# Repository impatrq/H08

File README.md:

# H-08

Reacondicionamiento aviónico del Sikorsky S-55 de la escuela. Proyecto de 7.º 1.ª, Aviónica, comisión B, de la E.E.S.T. N° 7 "IMPA" (Taller Regional Quilmes), 2026.

- Página: [proyecto-h08.github.io](https://proyecto-h08.github.io/)
- Instagram: [@proyectoh08](https://www.instagram.com/proyectoh08/)
- Mail: h08proyecto2026@gmail.com
- Video de presentación: [YouTube](https://www.youtube.com/watch?v=HCQF5zqOE_o)

## Qué es

H-08 es la matrícula de un Sikorsky S-55 (H-19A) que está en el taller de la escuela. Casi todos los instrumentos originales ya no funcionan, así que armamos el tablero de nuevo para usarlo en clase. Sobre la chapa original van 21 instrumentos con piezas que imprimimos en 3D, y las agujas las mueven servos SG90. La brújula usa un motor paso a paso y hay seis luces de alerta.

Todo lo maneja una Raspberry Pi 5. Tiene un modelo simple del helicóptero (motor, rotor, transmisión, aceite, combustible, parte eléctrica y actitud) y con eso calcula qué tiene que marcar cada instrumento. El profesor elige la fase del vuelo y mete fallas desde el celular, por ejemplo una falla de generador o de bomba de aceite, y los alumnos ven cómo responde cada aguja en el tablero y en su celular.

La Raspberry arma su propia red wifi, así que no hace falta internet:

- red: Tablero-H08
- clave: sikorsky55
- dirección: http://10.55.0.1 (en la mayoría de los celulares se abre sola al conectarse)

## Cómo está armado

La Raspberry habla por I2C con dos placas PCA9685 (direcciones 0x40 y 0x41) que generan el pulso de los 20 servos y prenden las luces. El motor de la brújula es un 28BYJ-48 con su driver ULN2003, conectado a los GPIO 12, 16, 20 y 21. La llave BATERÍA del panel va al GPIO 26 y sirve para apagar todo en orden. Los servos se alimentan aparte, nunca desde la Pi: una fuente de 12 V alimenta un regulador LM2596 que baja a 5 V.

Las conexiones pasan por una placa madre que diseñamos en KiCad (170 x 110 mm, una sola cara).

En los instrumentos donde la aguja tiene que dar más vuelta que lo que gira un servo usamos engranajes impresos: 36/24, 40/24 y 48/24. El horizonte artificial muestra solo el alabeo: el plato va pegado al servo. La brújula gira sin fin con el paso a paso.

La pantalla HDMI de la Raspberry muestra el tablero completo, con las mismas carátulas que pegamos en los instrumentos y un helicóptero en 3D que vuela con la simulación.

## Carpetas

- [Docs](Docs/): carpeta técnica, carpeta de campo, manual de usuario, elementos de alcance inconclusos, anteproyecto e historias de usuario.
- [Kicad](Kicad/): el proyecto de la placa madre y los planos para hacerla.
- [Software](Software/): el programa de la Raspberry Pi 5.
- [Estructura](Estructura/): las piezas para imprimir (STL), las carátulas y cómo se arma cada instrumento.
- [Web](Web/): la página del proyecto.
- [Multimedia](Multimedia/): video de presentación, las diapositivas de la expo, fotos (la del equipo también), logos, banner y stickers.

## Lo que usamos

| Componente | Cant. |
|---|---|
| Raspberry Pi 5 de 4 GB con fuente oficial de 27 W | 1 |
| MicroSD de 16 GB | 1 |
| PCA9685 | 2 |
| Servo SG90 | 20 |
| Motor 28BYJ-48 con driver ULN2003 | 1 |
| LED 5 mm (ámbar, rojo y verde) | 6 |
| Fuente de 12 V 7 A | 1 |
| Regulador LM2596 (de 12 V a 5 V) | 1 |
| Llave de palanca (BATERÍA) | 1 |
| Pantalla HDMI | 1 |
| Placa madre | 1 |

Más las piezas impresas en PLA, los acrílicos de cada instrumento y los pegamentos. La lista completa con precios está en [Docs/Plantilla_de_compras_H08.xlsx](Docs/Plantilla_de_compras_H08.xlsx).

## Para ponerlo en marcha

Primero se imprimen y arman los instrumentos con las piezas de Estructura, y se hace la placa con los planos de Kicad/Planos.

Después se copia `Software/H08_Pi5` a la Raspberry, que tiene que tener Raspberry Pi OS con escritorio de 64 bits, y se instala:

```bash
cd ~/H08_Pi5/raspberry_pi5
bash instalar.sh
sudo reboot
```

Con `python3 diagnostico_pi.py` se revisan las conexiones y con `python3 calibrar_instrumento.py --todos` se calibran las agujas una por una. Todo eso está explicado más largo en [Software/H08_Pi5/LEEME.md](Software/H08_Pi5/LEEME.md) y en el manual de usuario.

## Equipo

- Mateo Ghirelli: software (programa en Python, WiFi y simulación)
- Fausto Taranto: hardware (circuito, calibración y cableado)
- Constantino da Costa: integración, pruebas, redes y presentación
- Thomas Lehmann: restauración mecánica y montaje
- Agustín Merodo: relevamiento, montaje y documentación

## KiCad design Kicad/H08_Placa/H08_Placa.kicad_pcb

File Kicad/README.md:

# Placa madre

El proyecto de KiCad de la placa madre del tablero: esquemático y placa ruteada, con las librerías que hicimos adentro de la misma carpeta.

En `H08_Placa` está el proyecto. Se abre `H08_Placa.kicad_pro` y con eso aparecen el esquemático y la placa. Las librerías propias son `H08.kicad_sym` (símbolos) y la carpeta `H08.pretty` (huellas con las medidas de los componentes reales). `CONEXIONES.txt` tiene la red completa pata por pata y en `LEEME.txt` está el detalle del diseño y los pasos para hacerla.

En `Planos` están los PDF para fabricarla: el arte del cobre espejado para planchar, el cobre visto desde abajo, el plano de agujeros y el de montaje (dónde va cada componente).

La placa mide 170 x 110 mm y es de una sola cara. Tiene 242 pistas y 25 puentes de alambre, que son 15 del ruteo y 10 para coser el plano de masa. A la entrada de 5 V lleva un fusible lento de 4 A (F1) y después un supresor P6KE6.8A (D2).

Para abrirla usamos KiCad 10. El proyecto está guardado en formato de KiCad 6, así que la primera vez pregunta si lo actualiza y se le dice que sí. No hay que instalar ninguna librería. Al abrir la placa hay que apretar B para que rellene el plano de masa.

Para hacerla no hace falta exportar nada: `Planos/arte_bcu_espejado.pdf` ya está a escala 1:1. Antes de transferirlo conviene medir el contorno con una regla, tiene que dar 170 x 110 mm. Se imprime al 100 %, no con "ajustar a la página".

En la placa que armamos no van U1 y U2 (los ULN2003) ni las borneras J11 y J12 de los motores. El motor de la brújula usa la plaquita ULN2003 que viene con él y se conecta con cables a los pines que pusimos en el lugar de U2.

**Ojo con el conector de la Raspberry (J1).** Cuando hicimos la placa, el dibujo quedó dado vuelta, como en un espejo. Por eso los pines de J1 no quedaron en el mismo orden que los de la Raspberry, y el cable plano de 40 hilos no sirve: conectaría cada señal en el lugar equivocado.

Lo resolvimos con cables sueltos (Dupont hembra-hembra), uno por pin. Cada cable une el pin de la Raspberry con el pin de la placa que tiene el mismo nombre, por ejemplo SDA con SDA. El nombre de cada pin está escrito en la placa. La lista de qué va con qué está en [Software/H08_Pi5/LEEME.md](../Software/H08_Pi5/LEEME.md#cableado-de-la-raspberry-a-la-placa-madre).

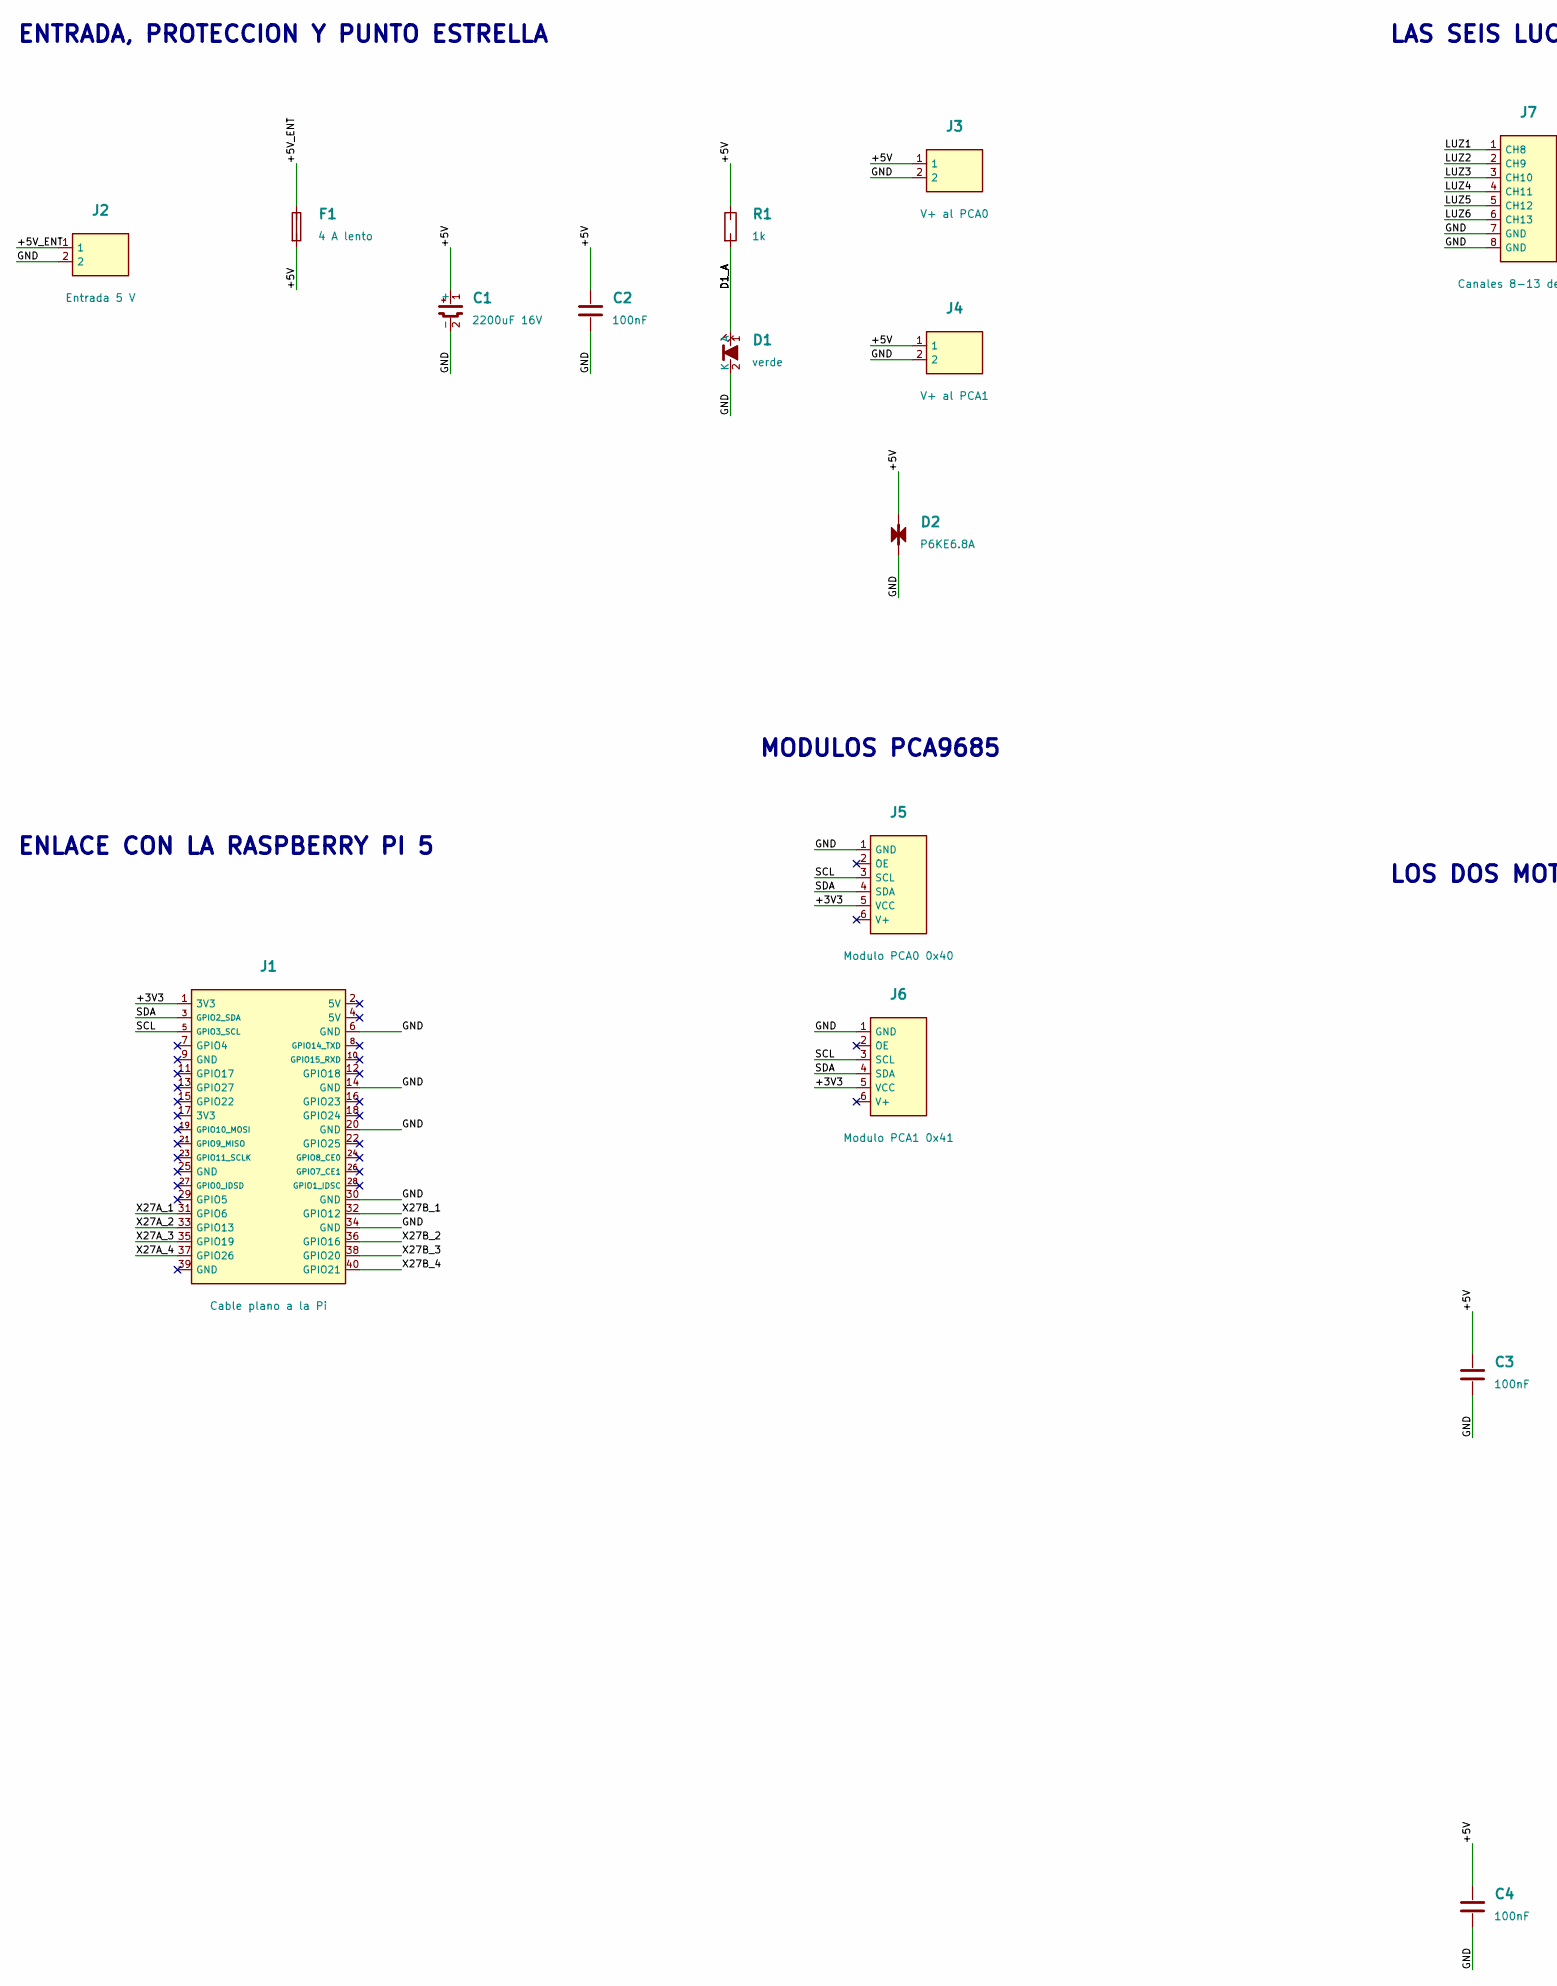
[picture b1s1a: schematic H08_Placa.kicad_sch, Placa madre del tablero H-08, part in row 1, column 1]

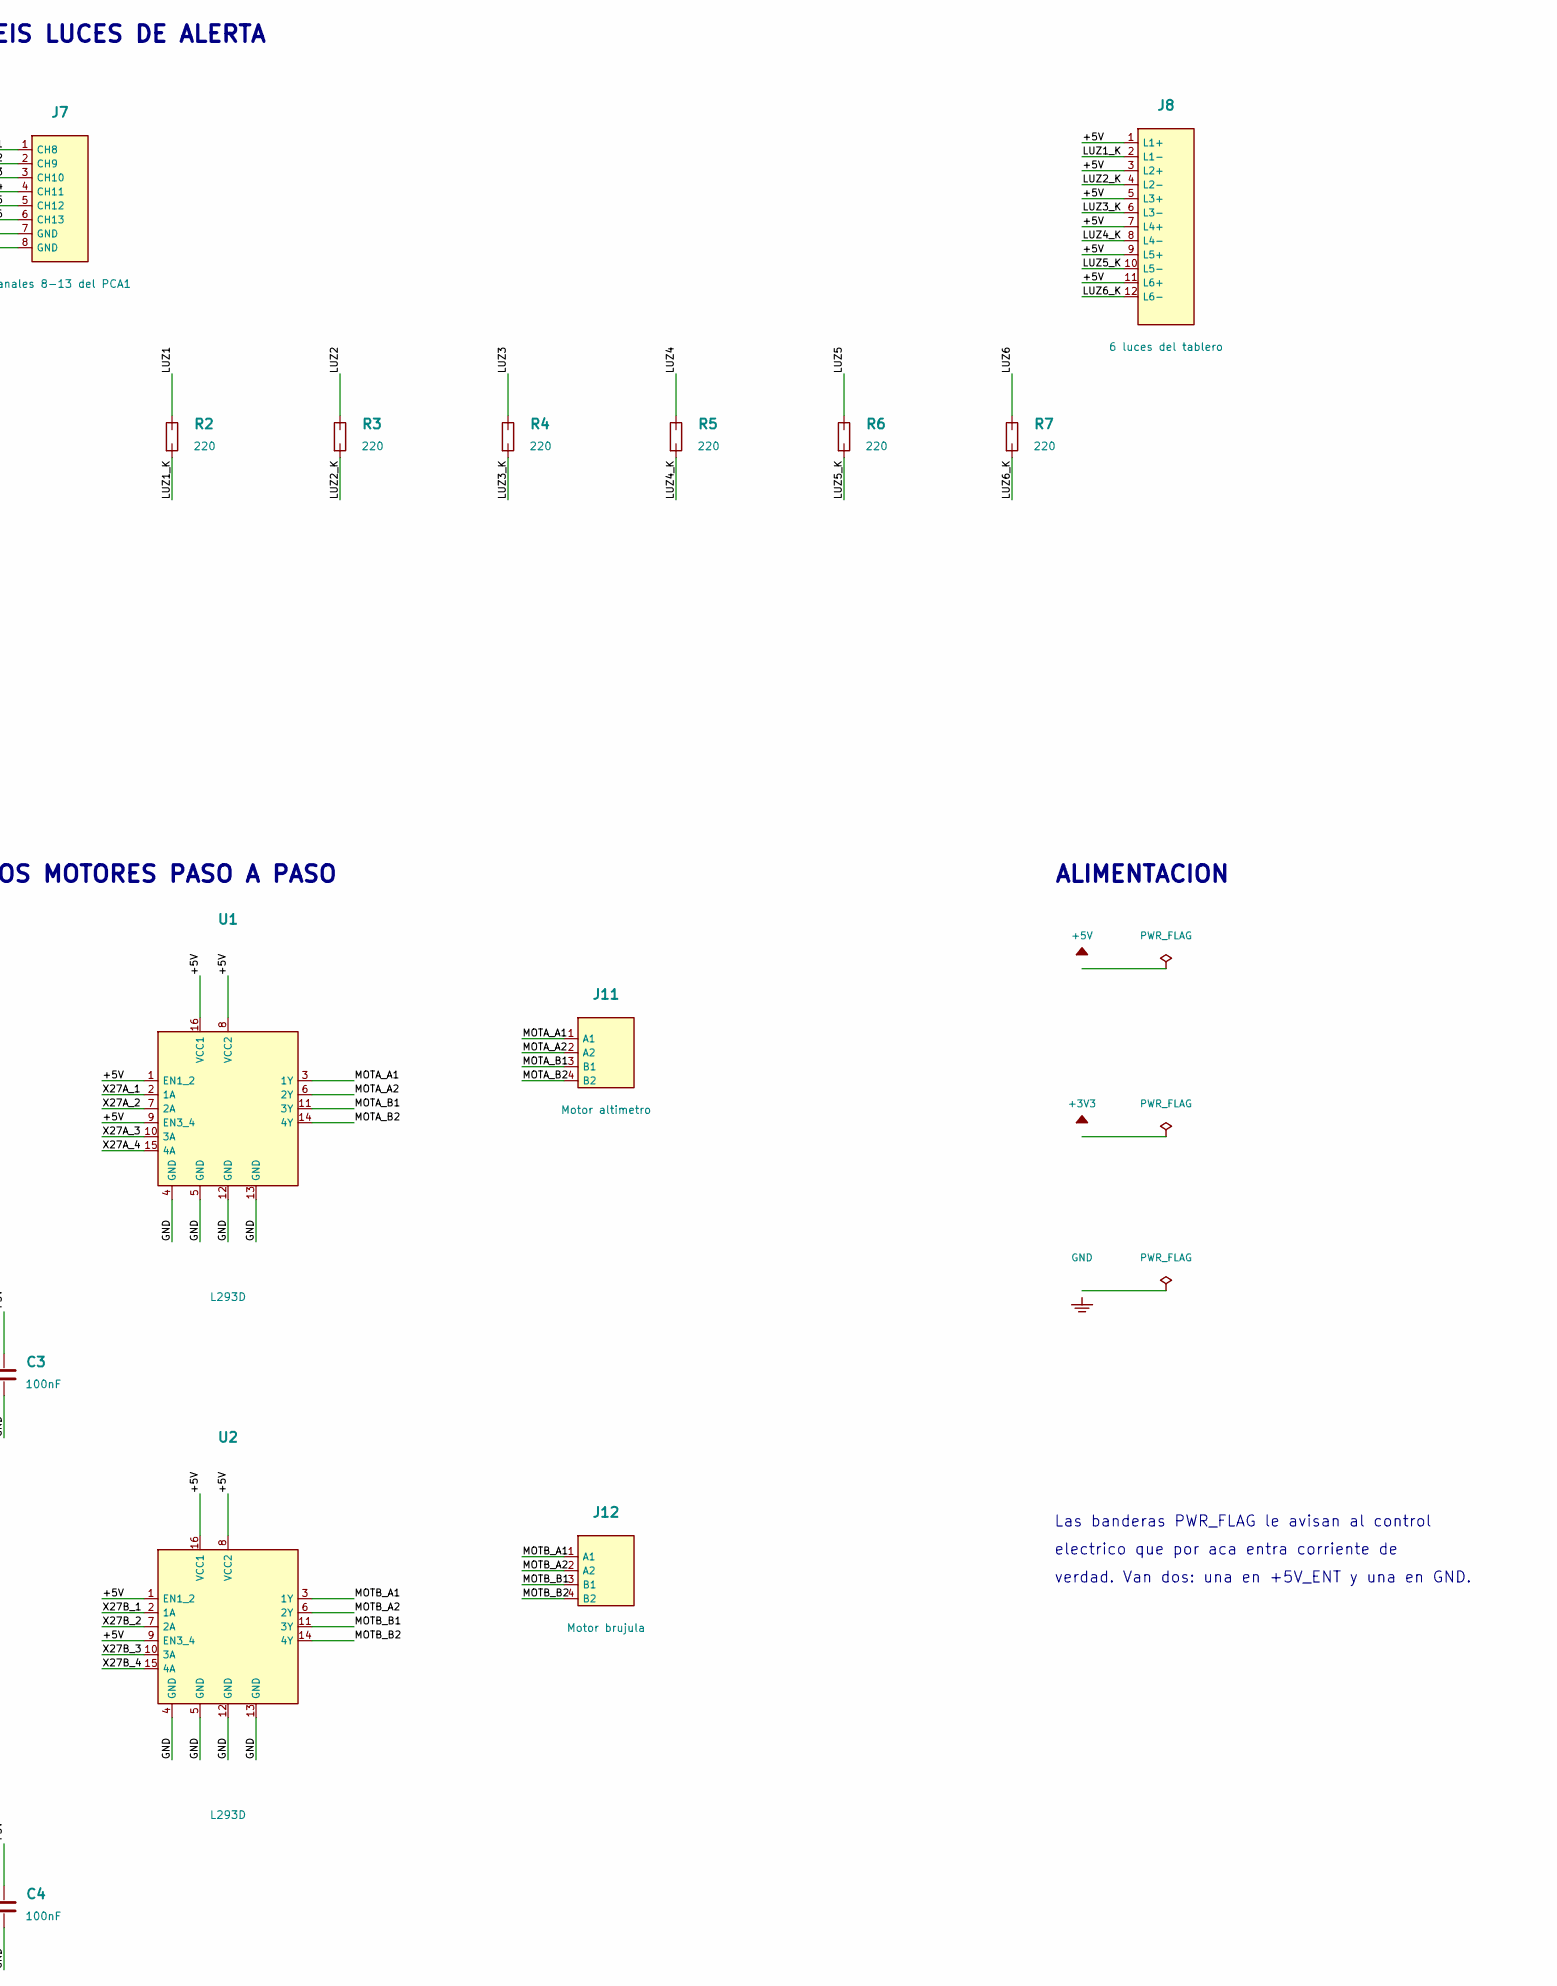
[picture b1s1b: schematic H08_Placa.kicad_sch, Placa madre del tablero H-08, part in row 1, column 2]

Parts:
C1: 2200uF 16V; C_Electrolitico_D16_P7.5mm
C2, C3, C4: 100nF; C_Disco_P5.08mm
D1: verde; LED_5mm
D2: P6KE6.8A; TVS_DO15_P10.16mm
F1: 4 A lento; Portafusible_5x20mm
J1: Cable plano a la Pi; Tira_2x20_2.54mm
J2: Entrada 5 V; Bornera_2x5.08mm
J3: V+ al PCA0; Bornera_2x5.08mm
J4: V+ al PCA1; Bornera_2x5.08mm
J5: Modulo PCA0 0x40; Modulo_PCA9685_6pin
J6: Modulo PCA1 0x41; Modulo_PCA9685_6pin
J7: Canales 8-13 del PCA1; Tira_1x08_2.54mm
J8: 6 luces del tablero; Bornera_12x5.08mm
J11: Motor altimetro; Bornera_4x5.08mm
J12: Motor brujula; Bornera_4x5.08mm
R1: 1k; R_Axial_P10.16mm
R2, R3, R4, R5, R6, R7: 220; R_Axial_P10.16mm
U1, U2: L293D; DIP-16_Zocalo

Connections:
+3V3: J1.1 (3V3), J5.5 (VCC), J6.5 (VCC)
+5V: C1.1 (+), C2.1, C3.1, C4.1, D2.1 (K), F1.2, J3.1, J4.1, J8.1 (L1+), J8.3 (L2+), J8.5 (L3+), J8.7 (L4+), J8.9 (L5+), J8.11 (L6+), R1.1, U1.1 (EN1_2), U1.8 (VCC2), U1.9 (EN3_4), U1.16 (VCC1), U2.1 (EN1_2), U2.8 (VCC2), U2.9 (EN3_4), U2.16 (VCC1)
+5V_ENT: F1.1, J2.1
D1_A: D1.1 (A), R1.2
GND: C1.2 (-), C2.2, C3.2, C4.2, D1.2 (K), D2.2 (A), J1.6 (GND), J1.14 (GND), J1.20 (GND), J1.30 (GND), J1.34 (GND), J2.2, J3.2, J4.2, J5.1 (GND), J6.1 (GND), J7.7 (GND), J7.8 (GND), U1.4 (GND), U1.5 (GND), U1.12 (GND), U1.13 (GND), U2.4 (GND), U2.5 (GND), U2.12 (GND), U2.13 (GND)
LUZ1: J7.1 (CH8), R2.1
LUZ1_K: J8.2 (L1-), R2.2
LUZ2: J7.2 (CH9), R3.1
LUZ2_K: J8.4 (L2-), R3.2
LUZ3: J7.3 (CH10), R4.1
LUZ3_K: J8.6 (L3-), R4.2
LUZ4: J7.4 (CH11), R5.1
LUZ4_K: J8.8 (L4-), R5.2
LUZ5: J7.5 (CH12), R6.1
LUZ5_K: J8.10 (L5-), R6.2
LUZ6: J7.6 (CH13), R7.1
LUZ6_K: J8.12 (L6-), R7.2
MOTA_A1: J11.1 (A1), U1.3 (1Y)
MOTA_A2: J11.2 (A2), U1.6 (2Y)
MOTA_B1: J11.3 (B1), U1.11 (3Y)
MOTA_B2: J11.4 (B2), U1.14 (4Y)
MOTB_A1: J12.1 (A1), U2.3 (1Y)
MOTB_A2: J12.2 (A2), U2.6 (2Y)
MOTB_B1: J12.3 (B1), U2.11 (3Y)
MOTB_B2: J12.4 (B2), U2.14 (4Y)
SCL: J1.5 (GPIO3_SCL), J5.3 (SCL), J6.3 (SCL)
SDA: J1.3 (GPIO2_SDA), J5.4 (SDA), J6.4 (SDA)
X27A_1: J1.31 (GPIO6), U1.2 (1A)
X27A_2: J1.33 (GPIO13), U1.7 (2A)
X27A_3: J1.35 (GPIO19), U1.10 (3A)
X27A_4: J1.37 (GPIO26), U1.15 (4A)
X27B_1: J1.32 (GPIO12), U2.2 (1A)
X27B_2: J1.36 (GPIO16), U2.7 (2A)
X27B_3: J1.38 (GPIO20), U2.10 (3A)
X27B_4: J1.40 (GPIO21), U2.15 (4A)

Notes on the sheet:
ENTRADA, PROTECCION Y PUNTO ESTRELLA
ENLACE CON LA RASPBERRY PI 5
MODULOS PCA9685
LAS SEIS LUCES DE ALERTA
LOS DOS MOTORES PASO A PASO
ALIMENTACION
Las banderas PWR_FLAG le avisan al control
electrico que por aca entra corriente de
verdad. Van dos: una en +5V_ENT y una en GND.

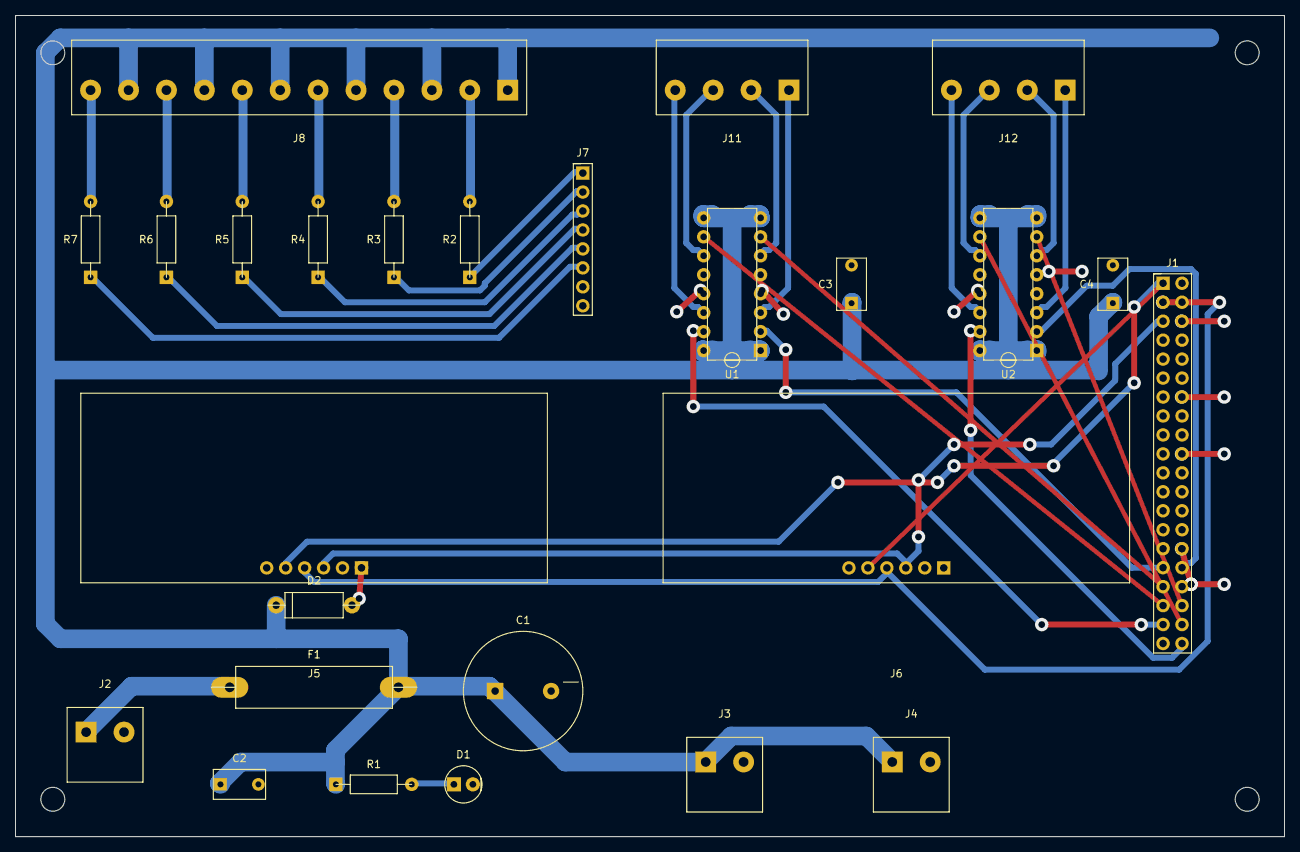
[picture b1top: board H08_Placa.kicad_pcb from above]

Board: 2 copper layers, 170.0 x 110.0 mm, 26 parts (0 on the bottom side), 35 nets.

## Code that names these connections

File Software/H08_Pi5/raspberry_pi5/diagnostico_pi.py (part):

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   SDA  (I2C)        GPIO2    3
   SCL  (I2C)        GPIO3    5
   GND               -        6, 9, 14, 20, 25, 30, 34, 39
   Motor IN1         GPIO12   32
   Motor IN2         GPIO16   36
   Motor IN3         GPIO20   38
   Motor IN4         GPIO21   40
   Llave BATERÍA     GPIO26   37   (la otra pata de la llave a GND, pata 39)
   (libre: motor 0)  GPIO6/13/19      31/33/35
  --------------------------------------------------------------------------
  OJO, PLACA ESPEJADA: el cobre de la placa salió en espejo, así que en J1 las
  columnas par e impar quedaron cambiadas y el cable plano NO sirve. Se
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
